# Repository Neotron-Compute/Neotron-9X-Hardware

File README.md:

# Neotron 9X

## A powerful, yet simple, ARM-powered home computer.

The Neotron 9X brings the classic early 1990s home-computer design up-to-date. Our tech is based on the tried and true single board ARM computer model offering a hacker friendly platform for your retro project. It aims to bring the retro computing feel, with DOS and BASIC like environments and semi-modern interfaces, like SD cards and SVGA. And all the system software is Open Source and written in the Rust Programming Language, and all the hardware is Open Source too.

With an ARM9 based CPU, the Neotron-9X gives you power, without stopping you getting you right back into the hardware. With only 64 MiB of RAM, the challenge is to squeeze the maximum out of the minimum amount of resources. We're planning for 1024x768 SVGA graphics (with 256 colours from a pallette of 262,144), 80x50 text mode, stereo 16-bit audio, plus dual-joystick and FAT filesystem support.

If the Neotron 32 was like a BBC Micro, or a ZX Spectrum, then the Neotron 9X is aiming squarely at the Acorn RISC PC, the Commodore Amiga 1200, and all those 486-based Multimedia PCs. It's a bit like an original Raspberry Pi, but with more retro-themed interfaces, a fully open-source design, and with a bespoke OS that is much simpler to hack on than the Debian Linux that the Pi runs.

## Hardware

  - **CPU:** Microchip SAM9X60D5M System-in-Package
  - **Processor Core**: 600 MHz ARM926EJ-S
     - 32 KiB Instruction Cache
     - 32 KiB Data Cache
     - Memory Management Unit
  - **RAM:** 64 MiB on-package DDR2
     - Also has 64 KiB on-die SRAM
  - **ROM:** 256 KiB Serial Flash
     - Can load BIOS from "boot.bin" on SD-Card, like an Amiga 1000 loads Kickstart from floppy disk
     - Can also load BIOS into RAM from Serial Flash
  - **GPU:** Microchip SAM9 LCD Controller
     - 800x600 resolution (chip supports up to 1024x768 resolution maximum)
     - Typically 256 colour pallete mode to save Video RAM
     - Optional 16-bit mode for improved colour depth
     - Three hardware overlays with transparency
     - Hardware scaling
  - **GPU RAM:** Shared with main SDRAM
  - **Video Output:** SVGA
    - Nominally 800x600 at 60 Hz
    - Other resolutions TBD (pixel clock is limited to integer divisors of system clock)
    - Texas Instruments THS7316 Video Amplifier used to drive 75 ohm VGA output
    - Triple 6-bit 0.1% R2R DACs, to give max 262,144 (2^18) colours
  - **Storage:** SD Card slot, supports FAT16/FAT32 and MS-DOS partition tables
  - **USB:** 1x external USB 2.0 Full-speed Type-A Host ports (with a header for two more)
  - **Audio:** 16-bit 48 kHz stereo
    - Wolfson WM8731 Audio CODEC
    - 3.5mm stereo Line Out
    - 3.5mm stereo Amplified headphone output
    - Digital volume control
  - **Keyboard/Mouse:** 2x PS/2 Ports (2x 6-pin mini-DIN)
  - **MIDI**: MIDI In and MIDI Out (2x 5-pin 180-degree DIN)
  - **Serial**: RS-232 on 10-pin 2.54mm header suitable for DE-9 plug on IDC ribbon
  - **Ethernet**: Standard 100base-TX RJ45 port.
  - **Parallel**: 3.3v PC-style Parallel Port with DB-25 port
     - Also functions as 3.3v GPIO with 12 outputs and 4 inputs.
  - **Joystick**: 2x 9-pin game ports
     - supports Atari-compatible two-button joysticks, or SEGA MegaDrive/Genesis controllers
  - **Expansion**: 2x internal 2.54mm 2x6 headers carrying power, SPI, I2C and a dedicated IRQ line
  - **RTC**: Coin-cell battery backup for the main CPU's RTC.
  - **Mechanical Form Factor:** Fits Hammond [1598D] case

[1598D]: ./datasheets/Hammond%201598D.pdf

## Parts Required

  - **PCBA**: Load the [Neotron-9X schematic](./Kicad/neotron-9x.sch) in Kicad, or see the [Neotron-9X Release Area] on Github for PDFs, Gerbers and a CSV bill-of-materials.
     - TBD: We might put the SiP on a smaller 4-layer or 6-layer board which we will load with the other surface mount parts (like the power management unit), and allow you to make/buy the bare motherboard which takes all through-hole parts or chunky SSOP/TSSOP surface mount parts.
  - **Case**: Hammond [1598D], in your choice of colour. The case will include mounting screws, feet and two un-cut end panels.
  - **End panels**: TBD. We'll probably supply those as Gerbers so you can make end panels at your favourite PCB fab house at the same time you order the main PCB(s).
  - **SD Card**: Any SD or SDHC card should work.
  - **Monitor**: You will need monitor with 15-pin VGA input. The nominal resolution is 800 by 600 at 60 Hz (with a 40.00 MHz pixel clock), so an older 4:3 aspect ratio screen is best.
  - **Power Supply**: You need a standard mobile phone charger or other USB power source, and a standard USB A to B cable (like you would use for a USB printer). System requires 500mA minimum.
  - **Ribbon cables**: The DE9 RS-232 Serial port requires a 2.54mm pin header to D-Sub ribbon cable. You can scavenge one from an old PC, or buy them new from Amazon, eBay or AliExpress for a few UK pounds. _Note: You may find them incorrectly listed as a DB9 connector; a D-Sub B-Shell is the big one used on a IBM PC Parallel Port and larger 25-pin Serial Ports, whilst the 9-pin serial ports are always D-Sub E-Shells_.
  - **Keyboard and Mouse**: Any PS/2 Keyboard and PS/2 Mouse should work.
  - **Joysticks**: Any Atari-compatible 9-pin digital joystick should work and you can connect up to two at once, for two player gaming. Sega MegaDrive/Genesis controllers will also work.
  - **Audio**: You can plug in headphones to the headphone jack, or amplified speakers to the line-out jack.
  - **MIDI**: If you want to hook up a MIDI Synthesiser like a Roland MT-32, or a MIDI Keyboard, you just need standard 5-pin DIN MIDI cables.
  - **USB**: You have one external on-board USB port - you can use a standard PC case USB header cable if you want to add two more.

You can find a complete BOM (including all the connectors, but excluding the PCBs, case and Serial ribbon cables), on [Octopart]. Gerbers and BOM are also available on [OpenHardware] and [Kitspace]. Don't forget, if you get the Hammond case, you'll need to drill out or mill the endplates yourself to take the connectors.

_TODO: The above links won't work / are wrong._

[Neotron-32 Release Area]: https://github.com/Neotron-Compute/Neotron-9X-Hardware/releases
[Octopart]: https://octopart.com/bom-tool/tBdBR3vl
[OpenHardware]: https://www.openhardware.io/view/783/Neotron-9X
[Kitspace]: https://kitspace.org/boards/github.com/neotron-compute/neotron-9x-hardware/

## Git Setup

We recommend you have the following Git config set:

```console
$ git config --global filter.kicad_project.clean "sed -E 's/^update=.*$/update=Date/'"
$ git config --global filter.kicad_project.smudge cat
$ git config --global filter.kicad_sch.clean "sed -E 's/#(PWR|FLG)[0-9]+/#\1?/'"
$ git config --global filter.kicad_sch.smudge cat
```

See https://jnavila.github.io/plotkicadsch/ for details.

## Software

You will need to compile the Neotron 9X BIOS as save it to a FAT32 formatted SD card as "boot.bin". You will also need the Neotron OS saved as "neotron.img". The BIOS will be loaded into RAM by the on-board ROM bootloader. The BIOS will then bring up the system and chain-load the OS from SD card.

Once running the OS, you can load applications from the SD card. Applications can be written in C or in Rust, using the [Neotron SDK](https://github.com/neotron-compute/Neotron-SDK).

## Licence

This schematic and PCB design is Copyright (c) Jonathan 'theJPster' Pallant and other Neotron 9X contributors.

This work is licensed under a [Creative Commons Attribution-ShareAlike 4.0 International License](http://creativecommons.org/licenses/by-sa/4.0/).

## Contribution Agreement

Unless you explicitly state otherwise, any contribution intentionally submitted for inclusion in the work by you, as defined in the Apache-2.0 license, shall be licensed as above, without any additional terms or conditions.

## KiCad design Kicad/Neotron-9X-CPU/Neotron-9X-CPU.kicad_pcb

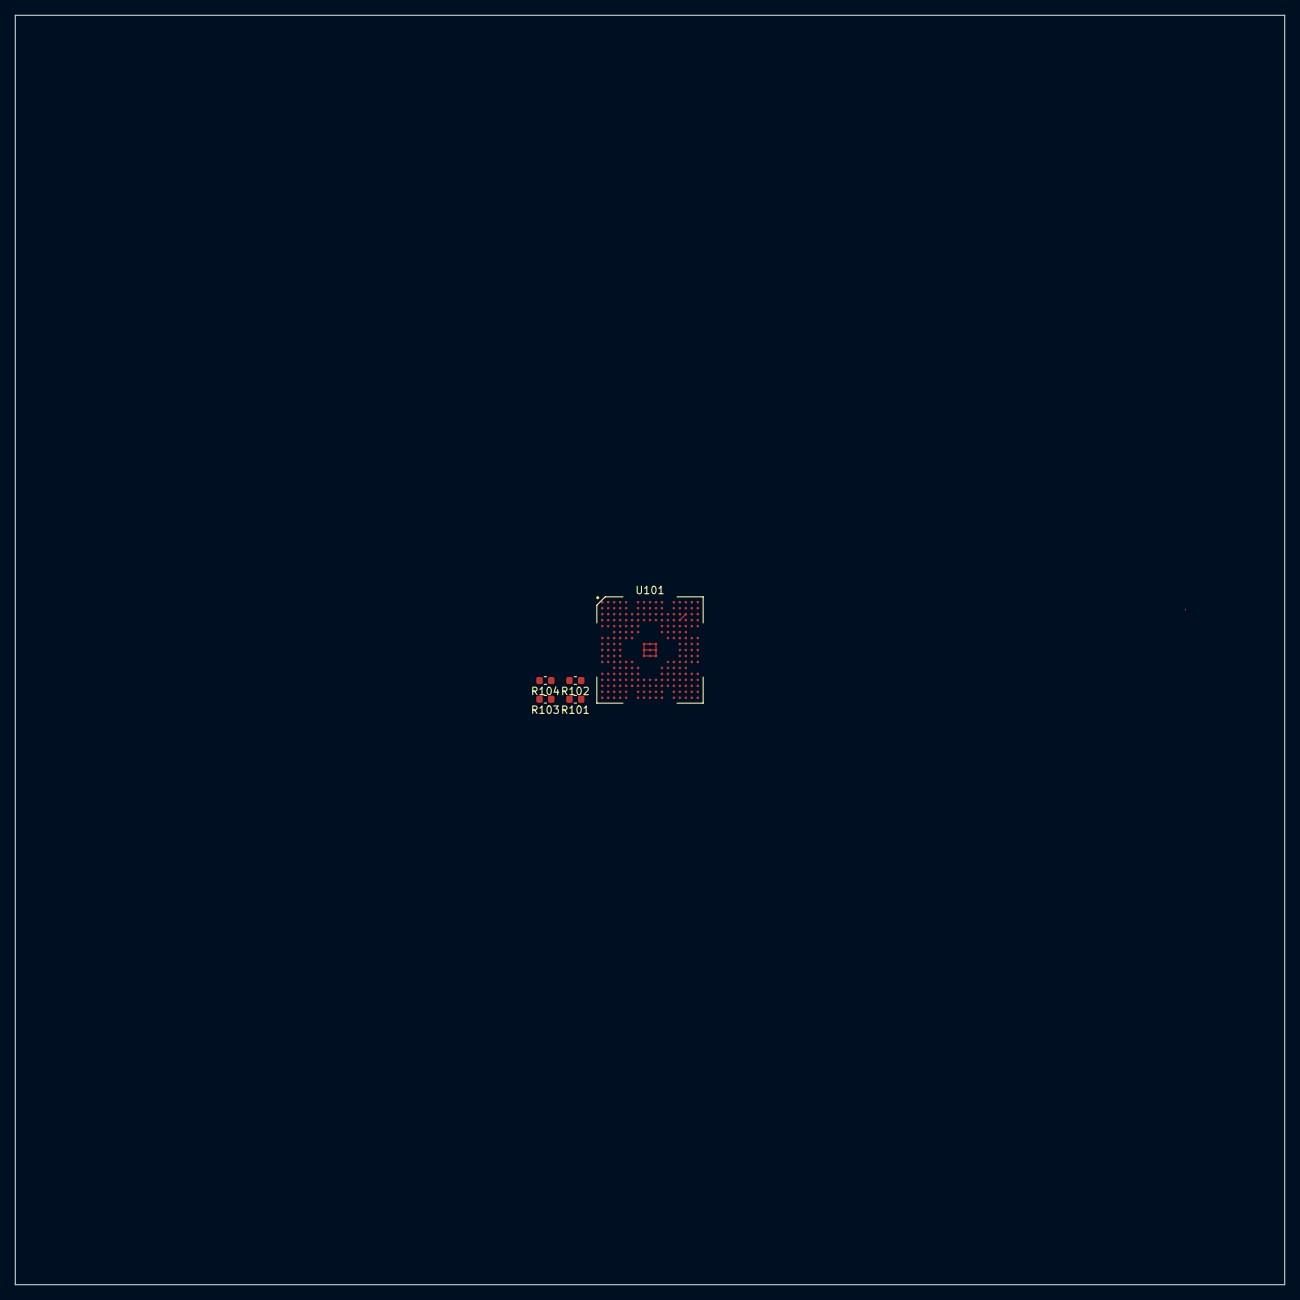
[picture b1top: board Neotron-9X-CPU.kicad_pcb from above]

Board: 2 copper layers, 170.0 x 170.0 mm, 5 parts (0 on the bottom side), 7 nets.

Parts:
R101, R102, R103, R104: 100; R_0603_1608Metric
U101: SAM9X60D5M; BGA-233_17x17_14.0x14.0mm

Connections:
+1V1: U101.C2, U101.D6, U101.D8, U101.G5, U101.L6, U101.M7, U101.R6
+1V8: U101.A16, U101.B15, U101.B17, U101.C14, U101.C16, U101.D13, U101.D15, U101.E11, U101.E12, U101.F13, U101.G13
+3V3: R101.1, R102.1, R103.1
/TDI: R101.2, U101.L15
/TMS: R102.2, U101.N16
GND: U101.A1, U101.A13, U101.A15, U101.A17, U101.B2, U101.B13, U101.B14, U101.B16, U101.C3, U101.C9, U101.C12, U101.C13, U101.C15, U101.D4, U101.D14, U101.E5, U101.E6, U101.E7, U101.E13, U101.F3, U101.F6, U101.F7, U101.F11, U101.F12, U101.F15, U101.G6, U101.G12, U101.H8, U101.H9, U101.H10, U101.J3, U101.J8, U101.J9, U101.J10, U101.J15, U101.K8, U101.K9, U101.K10, U101.L5, U101.L12, U101.L13, U101.L14, U101.M5, U101.M6, U101.M11, U101.M12, U101.M13, U101.M14, U101.N5, U101.N6, U101.N7, U101.N12, U101.N13, U101.P4, U101.P7, U101.P10, U101.P14, U101.R3, U101.R9, U101.R11, U101.R15, U101.R16, U101.T2, U101.T16, U101.U1, U101.U15
~RST: R103.2, R104.1, U101.P1

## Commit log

2020-07-26 First draft - work in progres.
2020-07-26 Moved Kicad down a level
2020-07-30 Updates to README
    Added Wolfson CODEC
2020-07-30 Started mapping pinout - Port A complete
    See SAM9X60D5M Reference Manual, Table 6-2 Ball Description
    I believe a "Flexcom" is a UART/I2C/SPI peripheral (see https://www.kernel.org/doc/Documentation/devicetree/bindings/mfd/atmel-flexcom.txt)
2020-07-31 Completed pinout spreadsheet.
2020-07-31 Selected pins.
2020-07-31 Added CODEC datasheet
2020-08-01 Split into separate mainboard and CPU board projects.
2020-08-01 Starting on VGA DAC.
2020-08-01 Allocating a MIDI UART in the pinout
2020-08-01 Updating README
2020-08-01 Update release script to build both projects.
2020-08-07 Mark SCH and PRO files as Kicad.
2020-08-07 Porting over sub-sheets from Neotron 32, and wrote new VGA block.
    VGA block uses THS7316 amplifier.
2020-08-15 Re-work CPU interface to include RMII.
2020-08-15 Clean up properties.

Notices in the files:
Kicad/Neotron-9X-CPU/Neotron-9X-CPU.kicad_pcb:
CC-BY-SA 4.0
